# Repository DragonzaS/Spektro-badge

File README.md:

# Spektro-badge
Badge with 6x6 display and Over-The-Light programming.

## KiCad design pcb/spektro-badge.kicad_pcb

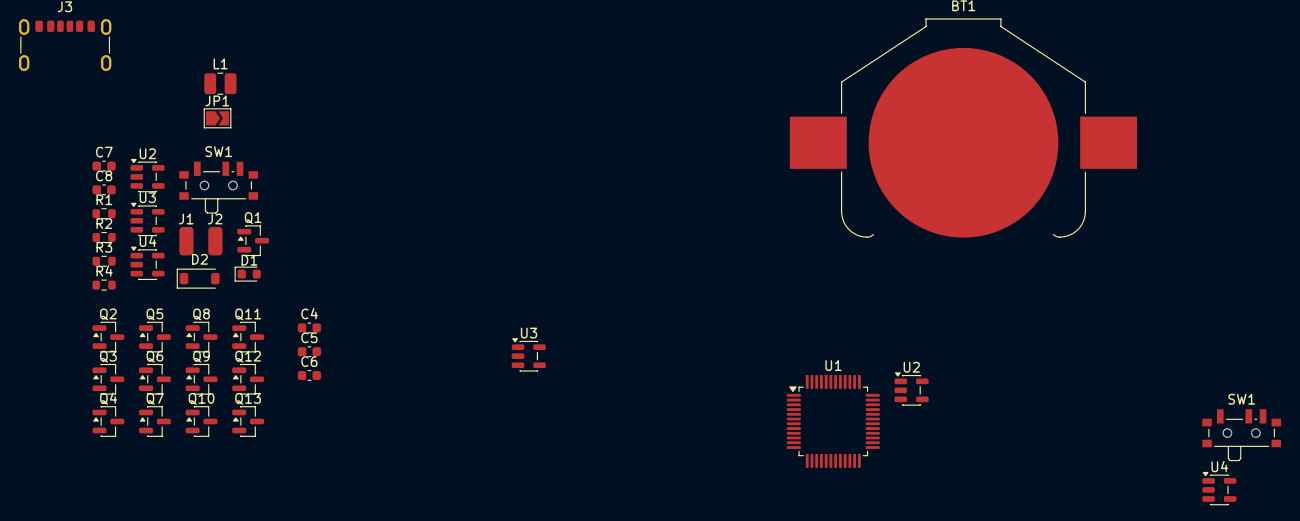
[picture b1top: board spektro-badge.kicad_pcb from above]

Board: 2 copper layers, 39 parts (0 on the bottom side), 14 nets, no tracks yet.

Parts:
BT1: Battery_Cell; BatteryHolder_Keystone_3008_1x2450
C4, C7: 4.7u; C_0603_1608Metric
C5: 10n; C_0603_1608Metric
C6: 1u; C_0603_1608Metric
C8: 10u; C_0603_1608Metric
D1: XL-1608SURC-06; LED_0603_1608Metric
D2: MBR0530T1G; D_SOD-123
J1, J2: Conn_01x01_Pin; SolderWirePad_1x01_SMD_1.5x3mm
J3: USB_C_Receptacle_PowerOnly_6P; USB_C_Receptacle_GCT_USB4125-xx-x-0190_6P_TopMnt_Horizontal
JP1: SolderJumper_2_Open; SolderJumper-2_P1.3mm_Open_TrianglePad1.0x1.5mm
L1: 2.2u; L_1008_2520Metric
Q1, Q2, Q3, Q4, Q5, Q6, Q7: AO3401A; SOT-23
Q8, Q9, Q10, Q11, Q12, Q13: AO3400A; SOT-23
R1: 4.42K; R_0603_1608Metric
R2, R4: 100K; R_0603_1608Metric
R3: 1.1K; R_0603_1608Metric
SW1, SW1#2: SW_SPDT; SW_SPDT_PCM12
U1: STM32F030C8Tx; LQFP-48_7x7mm_P0.5mm
U2, U2#2: MCP73832-2-OT; SOT-23-5
U3, U4: XB5350D0; SOT-23-5
U3#2, U4#2: SGMICRO SGM6013-3.3YTN5G/TR; SOT-23-5

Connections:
+3V3: C4.1, C5.1, C6.1, C8.1, L1.2, U1.1 (VDD), U1.9 (VDDA), U1.24 (VDD), U1.48 (VDD)
+BATT: J2.1 (Pin_1_1), Q1.3 (D), U2#2.3 (V_{BAT})
GND: C4.2, C5.2, C6.2, C7.1, C8.2, JP1.1 (A), R1.2, R4.1, SW1#2.1 (A), U1.8 (VSSA), U1.23 (VSS), U1.47 (VSS), U2#2.2 (V_{SS}), U3#2.2 (GND), U4.4 (VM), U4.5 (VM)
unnamed: D1.2 (A), R3.1
unnamed: D1.1 (K), U2#2.1 (STAT)
unnamed: J1.1 (Pin_1_1), JP1.2 (B), U4.2 (GND)
unnamed: J3.A12 (GND), J3.B12 (GND)
unnamed: J3.A9 (VBUS), J3.B9 (VBUS)
unnamed: R2.1, SW1#2.2 (B)
unnamed: R1.1, U2#2.5 (PROG)
unnamed: R2.2, U3#2.3 (RUN)
unnamed: L1.1, U3#2.5 (SW)
VCC: C7.2, D2.1 (K), Q1.2 (S), SW1#2.3 (C), U3#2.1 (VIN)
VUSB: D2.2 (A), Q1.1 (G), R3.2, R4.2, U2#2.4 (V_{DD})

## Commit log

2026-06-02 Add PCB folder
2026-06-10 updating the project with new schematics, still unfinished
